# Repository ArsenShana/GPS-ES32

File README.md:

# AlanaTech GPS — трекер на ESP32 + LoRa E32

```
 [NEO-6M] ──UART──> [ESP32 трекер] ──[E32 433 МГц]))) ~~~ (((  [E32]──> [ESP32 приёмник] ──Wi-Fi──> браузер
```

| Папка | Что это |
|---|---|
| [gps_tracker/](gps_tracker/) | ESP32 + NEO-6M + E32: раз в 5 с отправляет координаты по радио |
| [gps_receiver/](gps_receiver/) | ESP32 + E32: принимает пакеты, подключается к Wi-Fi `New BilimLand Wi-Fi`, показывает карту |

Оба проекта — PlatformIO (VS Code → расширение PlatformIO IDE).

## Плата без проводов и 3D-модель

В `tracker-lab/` добавлены локальный сайт с интерактивной 3D-моделью, симуляция
радиообмена, программно разведённая плата-носитель KiCad и корпус STL/STEP.
Запуск сайта: `cd tracker-lab` → `npm ci` → `npm start`, затем открыть
`http://localhost:4173`. Инструкция по сборке и прошивке: `tracker-lab/README.html`.

Носитель R0 рассчитан на **ESP32-DevKitC V4 WROOM с 38 контактами**, NEO-6M
breakout и E32-433T30D. Это прототип: разъёмы нужно сверить с вашими модулями,
KiCad DRC/ERC и физические испытания ещё не выполнены. Герберы пока не выпущены.
Для носителя добавлены среды `carrier` и `carrier_fake` с AUX на GPIO19;
передача пропускается при ошибке конфигурации E32 или таймауте AUX.

Вторая версия **AT-02 V2** находится в `tracker-lab/v2/` и открывается по
`http://localhost:4173/v2/`. Это собственная SMD-архитектура на STM32L072CBT6
с MAX-M10S, E32-433T20S, USB-C, LiPo/PowerPath, buck-boost 3.3 В и датчиком
движения. Arduino/ESP32-DevKit не используются. Подготовлены нумерованная
KiCad-схема, netlist, компоновка PCB 68×44 мм, корпус и отдельная 3D-модель.
Статус V2 — инженерный проект A0: финальная трассировка, RF, уточнение некоторых
посадочных мест и DRC/ERC ещё нужны; Gerber не выпущены. Ядро логики написано
на C и проверено на компьютере, но полный STM32-порт и физические испытания
пока не выполнены. ESP32-прошивку R0 нельзя загружать в V2.

## Подключение

E32 — одинаково на обеих платах:

| E32-433T30D | ESP32 трекер | ESP32 приёмник |
|---|---|---|
| VCC | **5V (VIN)** — не 3.3V! | **5V (VIN)** |
| GND | GND | GND |
| TXD | GPIO16 | GPIO16 |
| RXD | GPIO17 | GPIO17 |
| M0 | GPIO25 | GPIO25 |
| M1 | GPIO26 | GPIO26 |
| AUX | GPIO27 (можно не подключать) | GPIO27 (можно не подключать) |

Только на трекере — NEO-6M (без GPS прошивайте `tracker_fake`):

| NEO-6M | ESP32 |
|---|---|
| VCC | 3.3V (или 5V, если на модуле есть стабилизатор) |
| GND | GND |
| TX | GPIO32 |
| RX | GPIO33 |

> ⚠️ **Никогда не включайте E32 без антенны** — на мощности 1 Вт выходной каскад сгорит.
> ⚠️ E32-433T30D при передаче берёт до ~700 мА. Питание от USB ноутбука может «проседать» —
> тогда ESP32 перезагружается (brownout). Поставьте конденсатор 470–1000 мкФ между VCC и GND модуля.
> При тесте на столе антенны должны быть на расстоянии хотя бы 1–2 м (1 Вт вплотную перегружает приёмник).

Пины меняются в `include/config.h` каждого проекта.

## Параметры радио

Обе прошивки при старте сами проверяют и при необходимости записывают одинаковую конфигурацию E32:
433 МГц (канал 0x17), адрес 0x0000, UART 9600, скорость в эфире 2.4 кбит/с, FEC, 30 дБм, прозрачный режим.

Формат пакета (≤ 58 байт, один радиопакет E32) описан в `lib/GpsProtocol/GpsProtocol.h`:
```
G,1,1234,1,51.128207,71.430411,347,12.3,9,0.9*50
```

## Прошивка

Плата подключается по Type-C и видна как `USB-SERIAL CH340 (COMx)`. Если порт не появился —
кабель только для зарядки, нужен кабель с передачей данных.

**Режим прошивки.** На этих платах автоматический вход в загрузчик не срабатывает
(ошибка `Wrong boot mode detected (0x13)`), поэтому перед каждой прошивкой:
1. зажать **BOOT**;
2. нажать и отпустить **EN** (RST);
3. отпустить **BOOT** — плата ждёт прошивку, пока её не перезагрузят.

```bash
# трекер
cd gps_tracker
pio run -e tracker -t upload && pio device monitor

# приёмник
cd gps_receiver
pio run -e receiver -t upload && pio device monitor
```

Если PlatformIO не установлен в VS Code, вместо `pio` используйте `py -3.11 -m platformio`.

`lib/GpsProtocol` и `lib/E32` одинаковые в обеих папках — при изменении правьте обе копии.

Ход тестирования и найденные ошибки — в [TESTING.md](TESTING.md).

## Тестирование

### 1. Юнит-тесты протокола (без железа, на ПК)
```bash
cd gps_tracker  && pio test -e native
cd gps_receiver && pio test -e native
```
Проверяют кодирование/декодирование, отбрасывание битых и обрезанных пакетов, помещение в 58 байт, подсчёт потерь.
Нужен gcc в PATH (например, MSYS2 `C:\msys64\mingw64\bin`).

### 2. Проверка каждого модуля (Serial-монитор, 115200)
- Трекер: должно быть `[E32] конфигурация ОК` и строки `[GPS] символов=...` с растущим числом.
  Если `символов=0` — неправильно подключён TX NEO-6M.
- Приёмник: `[E32] конфигурация ОК`, `[WiFi] подключено, IP: ...`.
  Если Wi-Fi не подключился, прошивка печатает код причины и список видимых сетей
  (201 — сеть не найдена: проверьте имя с учётом регистра и что сеть на 2.4 ГГц).

### 3. Радиоканал без GPS (в помещении)
Прошейте трекер тестовой прошивкой — она шлёт координаты по кругу вокруг центра Астаны:
```bash
cd gps_tracker && pio run -e tracker_fake -t upload
```
В логе приёмника появятся строки `[RX] id=1 seq=... fix=1 ...`, на странице `http://<IP приёмника>/` — движущаяся точка.

### 4. Автоматическая проверка связи с ПК
ПК должен быть в той же Wi-Fi сети:
```bash
python gps_receiver/tools/link_test.py <IP приёмника> -t 120
```
В конце — итог: принято / потеряно / % потерь и вердикт.

### 5. Настоящий GPS
Прошейте `-e tracker`, вынесите трекер на улицу или к окну. Холодный старт NEO-6M — до 5 минут
(на модуле замигает светодиод, когда есть фикс). На странице бейдж станет «GPS фикс», на карте появится трек.

## Веб-интерфейс приёмника

| Адрес | Что |
|---|---|
| `/` | карта + данные |
| `/api/last` | последний пакет, JSON |
| `/api/history` | трек (до 200 точек), JSON |
| `/api/status` | статистика приёма, Wi-Fi |
| `POST /api/reset` | сброс статистики |

Также доступно по `http://alanatech-gps.local/` (если сеть/ОС поддерживает mDNS).
Карта грузится из интернета (OpenStreetMap), таблица работает и без него.

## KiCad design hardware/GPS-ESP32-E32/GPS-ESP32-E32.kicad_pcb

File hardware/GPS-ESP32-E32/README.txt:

GPS-ESP32-E32 — плата-носитель R0, 100 × 78 мм, 2 слоя, FR4 1.6 мм.

Открыть GPS-ESP32-E32.kicad_pro в KiCad. Рядом находятся редактируемая
схема .kicad_sch, разведённая плата .kicad_pcb, локальные библиотеки,
PDF схемы и платы, BOM.csv и отчёты DRC/ERC.

Модули: ESP32-DevKitC V4 WROOM, 38 контактов (19 на сторону,
25.4 мм между рядами); NEO-6M breakout; E32-433T30D.
J2/J3 — гнёзда ESP32, J4 — GPS, J5 — E32, J1 — вход 5 В.
GPS J4: 1=3V3, 2=RX, 3=TX, 4=GND.
E32 J5: 1=M0, 2=M1, 3=RXD, 4=TXD, 5=AUX, 6=5V, 7=GND.

Точная разводка GPIO:
GPS TX -> GPIO16, GPS RX <- GPIO17.
E32 TXD -> GPIO26, E32 RXD <- GPIO27.
E32 M0 <- GPIO25, E32 M1 <- GPIO18, E32 AUX -> GPIO19.
Индикатор: GPIO2 -> R1 330 Ом -> анод D1; катод D1 -> GND.

Прошивка из gps_tracker:
  pio run -e kicad_r0 -t upload
Для демонстрационных координат:
  pio run -e kicad_r0_fake -t upload
Обычные tracker/carrier имеют другую распиновку и не подходят этой разводке.

Питание: внешний стабилизированный источник 5 В / 2 А на J1.
E32 питается от 5 В, GPS — от 3.3 В ESP32. C1 1000 мкФ / 10 В
и C2 100 нФ установлены на шине 5 В возле радио.
JP1 соединяет внешний источник с 5V ESP32: снять перемычку до
подключения USB ESP32. Не подавать автомобильные 12/24 В напрямую.
Перед включением радио подключить подходящую антенну 433 МГц.

Проверено KiCad 10.0.6: DRC — 0 нарушений, 0 неподключённых;
ERC — 0 нарушений. Символы описывают пассивные контакты разъёмов:
ERC не проверяет внутренние цепи модулей и совместимость уровней.
Статус: прототип. До изготовления сверить габариты и порядок контактов
реальных модулей, гнёзда E32, полярность LED и конденсатора, проверить
питание и работу на стенде. Геометрия SMD-площадок упрощена.
Герберы для производства не выпускались.

Повторный экспорт проекта:
  python3 tracker-lab/tools/export_kicad_project.py
PDF и DRC/ERC обновляются отдельно через kicad-cli.

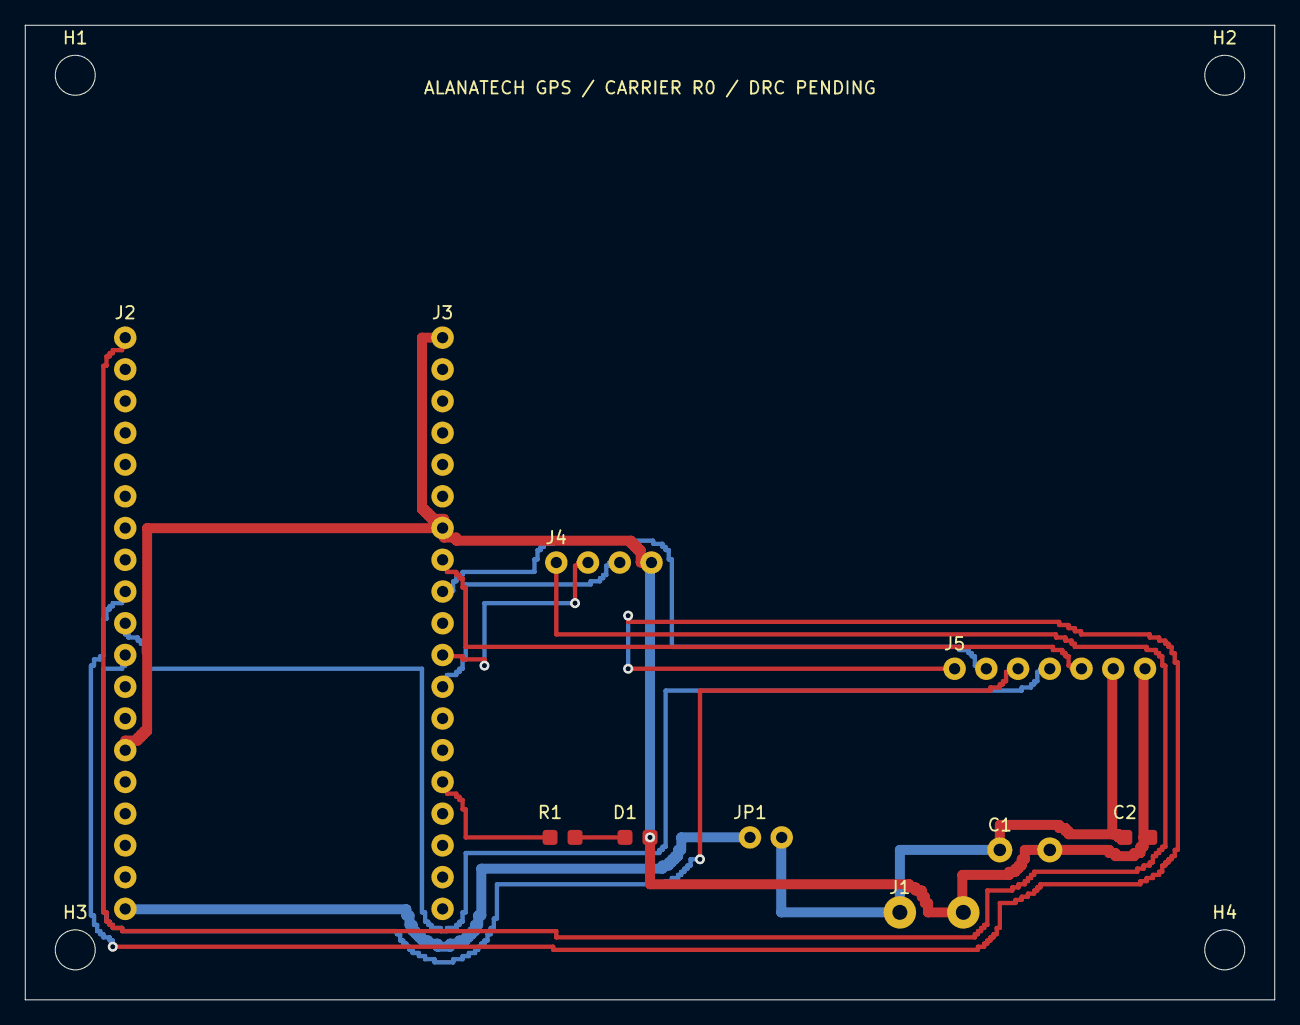
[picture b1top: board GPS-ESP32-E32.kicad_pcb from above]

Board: 2 copper layers, 100.0 x 78.0 mm, 14 parts (0 on the bottom side), 13 nets.

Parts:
C1: 1000uF_10V
C2: 100nF_0805
D1: LED_0805
H1, H2, H3, H4: M3
J1: 5V_INPUT_2A
J2: ESP32_J2_1x19
J3: ESP32_J3_1x19
J4: NEO6M_SOCKET_1x04
J5: E32_SOCKET_1x07_RIGHT_ANGLE
JP1: REMOVE_FOR_USB
R1: 330R_0805

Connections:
+3V3: J2.1, J4.1
+5V_ESP: J2.19, JP1.1
+5V_MAIN: C1.1, C2.1, J1.1, J5.6, JP1.2
E32_AUX: J3.8, J5.5
E32_M0: J2.9, J5.1
E32_M1: J3.9, J5.2
E32_RXD: J2.11, J5.3
E32_TXD: J2.10, J5.4
GND: C1.2, C2.2, D1.2, J1.2, J2.14, J3.1, J3.7, J4.4, J5.7
GPS_RX: J3.11, J4.2
GPS_TX: J3.12, J4.3
LED_A: D1.1, R1.2
LED_GPIO: J3.15, R1.1

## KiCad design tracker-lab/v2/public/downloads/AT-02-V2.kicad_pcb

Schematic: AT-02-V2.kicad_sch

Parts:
C1: 100nF / VDD1
C2: 100nF / VDD24
C3: 100nF / VDD48
C4: 100nF / USB VDD
C5: 100nF / VDDA
C6: 4.7uF / MCU
C7: 100nF / reset
C8: 100nF / ADC
C9: 1uF / GNSS VIO
C10: 10uF / GNSS VCC
C11: 1uF / GNSS backup
C12: 100nF / motion
C13: 10uF / motion
C14: 10uF / USB IN
C15: 10uF / battery
C16: 22uF / VSYS
C17: 10uF / buck-boost IN
C18, C19: 22uF / buck-boost OUT
C20: 100uF / radio buffer
C21: 100nF / radio
D1: Green LED / status
FB1: Ferrite / analog supply
J1: USB-C / USB 2.0
J2: LiPo / NTC · 3 контакта
J3: GNSS RF / u.FL
J4: SWD / pogo
L1: Дроссель 2.2 µH
R1: 5.1k / CC1
R2: 5.1k / CC2
R3: 22R / USB D+
R4: 22R / USB D-
R5: 10k / BOOT0
R6: 10k / NRST
R7: 1M / battery divider
R8: 330k / battery divider
R9: 10k / I2C SCL
R10: 10k / I2C SDA
R11: 330R / LED
R12: 100k / EN1 default
R13: 2.94k / ISET 300mA target
R14: 3.24k / ILIM
R15: 46.4k / safety timer
R16: 1k / ITERM
R17: 10k / CHG pullup
R18: 100R / GNSS QOD
R19: 10k / radio reset pullup
R20: 100k / M0 pulldown
R21: 100k / M1 pulldown
SW1: BOOT / DFU
SW2: RESET
U1: STM32L072CBT6
U2: u-blox MAX-M10S
U3: EBYTE E32-433T20S
U4: TI BQ24074
U5: TI TPS63031
U6: ST LIS2DW12
U7: TI TPS22919
U8: USBLC6-2SC6 / ESD

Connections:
+3V3: C1.1, C2.1, C3.1, C4.1, C6.1, C11.1, C12.1, C13.1, C18.1, C19.1, C20.1, C21.1, FB1.1, J4.1 (+3V3), R6.2, R9.2, R10.2, R17.2, R19.2, SW1.2 (3V3), U1.1 (VDD), U1.24 (VDD), U1.36 (VDD_USB), U1.48 (VDD), U2.6 (V_BCKP), U3.25 (VCC), U5.1 (VOUT), U5.10 (FB), U6.2 (CS), U6.9 (VDD), U6.10 (VDD_IO), U7.1 (VIN)
+3V3_A: C5.1, FB1.2, U1.9 (VDDA)
+3V3_GNSS: C9.1, C10.1, R18.2, U2.7 (V_IO), U2.8 (VCC), U7.6 (VOUT)
BAT_NTC: J2.3 (BAT_NTC), U4.1 (TS)
BOOT0: R5.1, SW1.1 (BOOT0), U1.44 (BOOT0)
CHARGE_EN1: R12.1, U1.45 (PB8), U4.6 (EN1)
CHG_ILIM: R14.1, U4.12 (ILIM)
CHG_ISET: R13.1, U4.16 (ISET)
CHG_ITERM: R16.1, U4.15 (ITERM)
CHG_STATUS: R17.1, U1.46 (PB9), U4.9 (CHG)
CHG_TMR: R15.1, U4.14 (TMR)
GND: C1.2, C2.2, C3.2, C4.2, C5.2, C6.2, C7.2, C8.2, C9.2, C10.2, C11.2, C12.2, C13.2, C14.2, C15.2, C16.2, C17.2, C18.2, C19.2, C20.2, C21.2, D1.2, J1.A1, J1.A12, J1.B1, J1.B12, J1.S1 (SHIELD), J1.S2 (SHIELD), J1.S3 (SHIELD), J1.S4 (SHIELD), J2.2 (GND), J3.2 (GND), J3.3 (GND), J4.5 (GND), R1.2, R2.2, R5.2, R8.2, R12.2, R13.2, R14.2, R15.2, R16.2, R20.2, R21.2, SW2.2 (GND), U1.8 (VSSA), U1.23 (VSS), U1.35 (VSS), U1.47 (VSS), U2.1 (GND), U2.10 (GND), U2.12 (GND), U3.2 (GND), U3.8 (GND), U3.11 (GND), U3.13 (GND), U3.14 (GND), U3.15 (GND), U3.16 (GND), U3.19 (GND), U3.26 (GND), U4.4 (CE), U4.5 (EN2), U4.8 (VSS), U4.17 (EP), U5.3 (PGND), U5.7 (PS_SYNC), U5.9 (GND), U5.11 (EP), U6.3 (SDO_SA0), U6.6 (GND), U6.7 (RES), U6.8 (GND), U7.2 (GND), U8.2
GNSS_EN: U1.16 (PA6), U7.3 (ON)
GNSS_PPS: U1.17 (PA7), U2.4 (TIMEPULSE)
GNSS_QOD: R18.1, U7.4 (QOD)
GNSS_RF: J3.1 (RF), U2.11 (RF_IN)
GNSS_RX: U1.30 (PA9), U2.3 (RXD)
GNSS_TX: U1.31 (PA10), U2.2 (TXD)
I2C_SCL: R9.1, U1.42 (PB6), U6.1 (SCL)
I2C_SDA: R10.1, U1.43 (PB7), U6.4 (SDA)
LED_A: D1.1, R11.2
LED_DRIVE: R11.1, U1.41 (PB5)
MOTION_INT: U1.19 (PB1), U6.12 (INT1)
NRST: C7.1, J4.4 (NRST), R6.1, SW2.1 (NRST), U1.7 (NRST)
RADIO_AUX: U1.11 (PA1), U3.24 (AUX)
RADIO_M0: R20.1, U1.14 (PA4), U3.20 (M0)
RADIO_M1: R21.1, U1.15 (PA5), U3.21 (M1)
RADIO_RESET: R19.1, U1.18 (PB0), U3.1 (RESET)
RADIO_RX: U1.12 (PA2), U3.22 (RXD)
RADIO_TX: U1.13 (PA3), U3.23 (TXD)
SWCLK: J4.3 (SWCLK), U1.37 (PA14)
SWDIO: J4.2 (SWDIO), U1.34 (PA13)
SW_L1: L1.1 (L1), U5.4 (L1)
SW_L2: L1.2 (L2), U5.2 (L2)
USB_CC1: J1.A5, R1.1
USB_CC2: J1.B5, R2.1
USB_DM: R4.2, U1.32 (PA11)
USB_DM_CONN: J1.A7, J1.B7, R4.1, U8.3, U8.4
USB_DP: R3.2, U1.33 (PA12)
USB_DP_CONN: J1.A6, J1.B6, R3.1, U8.1, U8.6
VBAT: C15.1, J2.1 (VBAT), R7.1, U4.2 (BAT), U4.3 (BAT)
VBAT_ADC: C8.1, R7.2, R8.1, U1.10 (PA0)
VBUS: C14.1, J1.A4, J1.A9, J1.B4, J1.B9, U4.13 (IN), U8.5
VSYS: C16.1, C17.1, U4.10 (OUT), U4.11 (OUT), U5.5 (VIN), U5.6 (EN), U5.8 (VINA)

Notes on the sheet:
AT-02 V2 A0 - CONNECTIVITY DRAFT / Verify package lands, RF, ERC pin types and complete routing before release

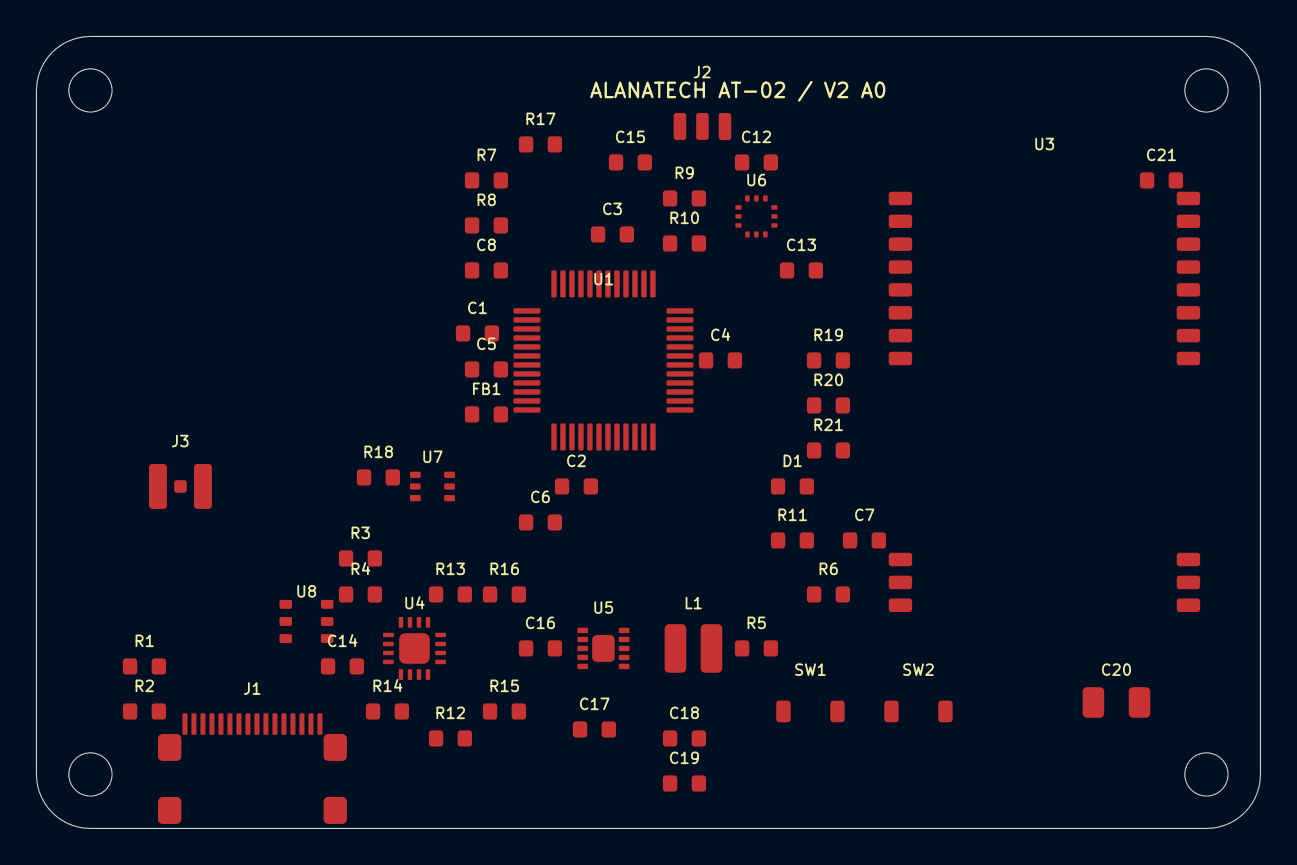
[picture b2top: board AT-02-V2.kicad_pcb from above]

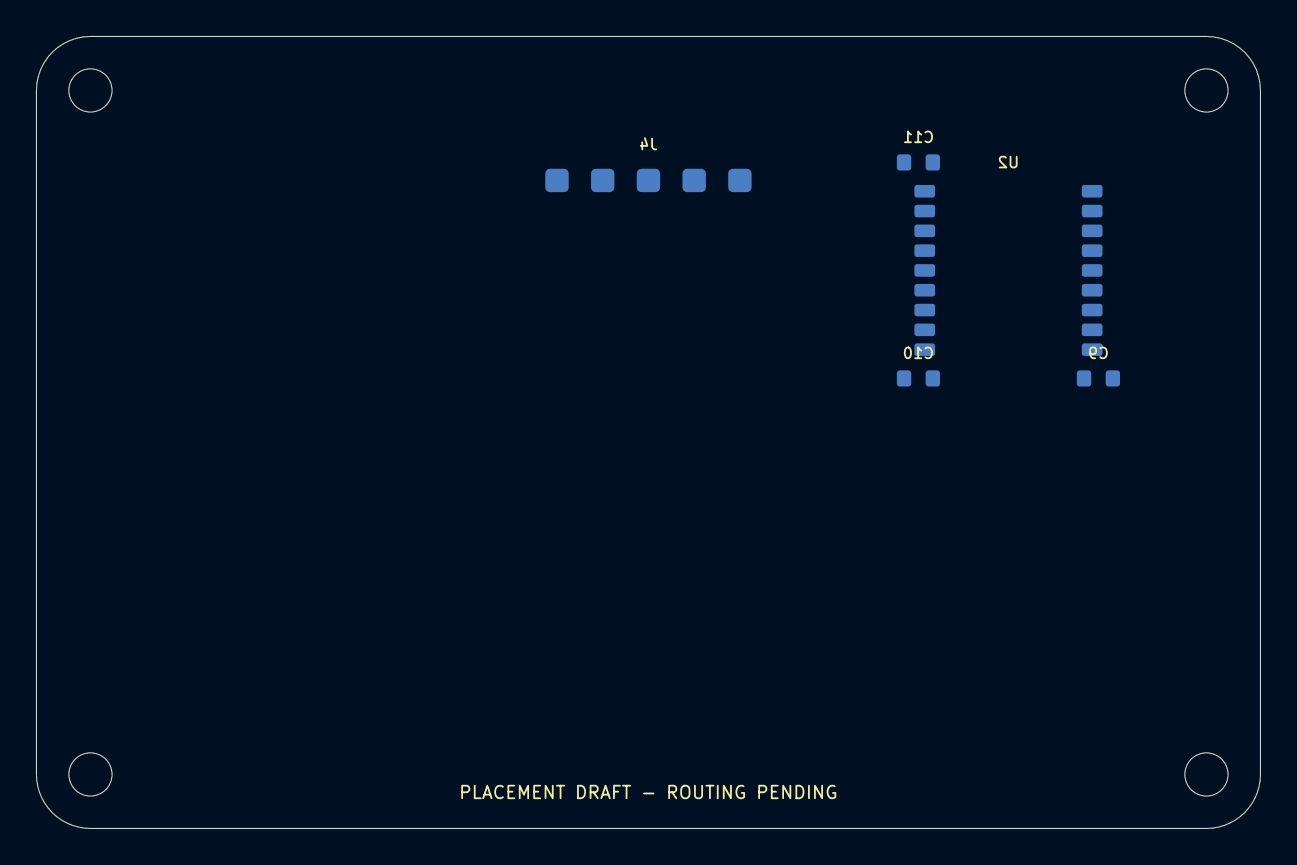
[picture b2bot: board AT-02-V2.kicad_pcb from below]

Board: 4 copper layers, 68.0 x 44.0 mm, 59 parts (5 on the bottom side), 44 nets, no tracks yet.

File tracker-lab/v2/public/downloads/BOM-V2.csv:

Ref,Value,Layer,X mm,Y mm,Status
U1,STM32L072CBT6,F.Cu,31.5,18,Selection/land pattern verification required
U2,u-blox MAX-M10S,B.Cu,14,13,Selection/land pattern verification required
U3,EBYTE E32-433T20S,F.Cu,56,20,Selection/land pattern verification required
U4,TI BQ24074,F.Cu,21,34,Selection/land pattern verification required
U5,TI TPS63031,F.Cu,31.5,34,Selection/land pattern verification required
U6,ST LIS2DW12,F.Cu,40,10,Selection/land pattern verification required
U7,TI TPS22919,F.Cu,22,25,Selection/land pattern verification required
J1,USB-C / USB 2.0,F.Cu,12,41,Selection/land pattern verification required
J2,LiPo / NTC · 3 контакта,F.Cu,37,5,Selection/land pattern verification required
L1,Дроссель 2.2 µH,F.Cu,36.5,34,Selection/land pattern verification required
J3,GNSS RF / u.FL,F.Cu,8,25,Selection/land pattern verification required
SW1,BOOT / DFU,F.Cu,43,37.5,Selection/land pattern verification required
SW2,RESET,F.Cu,49,37.5,Selection/land pattern verification required
R1,5.1k / CC1,F.Cu,6,35,Selection/land pattern verification required
R2,5.1k / CC2,F.Cu,6,37.5,Selection/land pattern verification required
R3,22R / USB D+,F.Cu,18,29,Selection/land pattern verification required
R4,22R / USB D-,F.Cu,18,31,Selection/land pattern verification required
R5,10k / BOOT0,F.Cu,40,34,Selection/land pattern verification required
R6,10k / NRST,F.Cu,44,31,Selection/land pattern verification required
R7,1M / battery divider,F.Cu,25,8,Selection/land pattern verification required
R8,330k / battery divider,F.Cu,25,10.5,Selection/land pattern verification required
R9,10k / I2C SCL,F.Cu,36,9,Selection/land pattern verification required
R10,10k / I2C SDA,F.Cu,36,11.5,Selection/land pattern verification required
R11,330R / LED,F.Cu,42,28,Selection/land pattern verification required
R12,100k / EN1 default,F.Cu,23,39,Selection/land pattern verification required
R13,2.94k / ISET 300mA target,F.Cu,23,31,Selection/land pattern verification required
R14,3.24k / ILIM,F.Cu,19.5,37.5,Selection/land pattern verification required
R15,46.4k / safety timer,F.Cu,26,37.5,Selection/land pattern verification required
R16,1k / ITERM,F.Cu,26,31,Selection/land pattern verification required
R17,10k / CHG pullup,F.Cu,28,6,Selection/land pattern verification required
R18,100R / GNSS QOD,F.Cu,19,24.5,Selection/land pattern verification required
R19,10k / radio reset pullup,F.Cu,44,18,Selection/land pattern verification required
R20,100k / M0 pulldown,F.Cu,44,20.5,Selection/land pattern verification required
R21,100k / M1 pulldown,F.Cu,44,23,Selection/land pattern verification required
C1,100nF / VDD1,F.Cu,24.5,16.5,Selection/land pattern verification required
C2,100nF / VDD24,F.Cu,30,25,Selection/land pattern verification required
C3,100nF / VDD48,F.Cu,32,11,Selection/land pattern verification required
C4,100nF / USB VDD,F.Cu,38,18,Selection/land pattern verification required
C5,100nF / VDDA,F.Cu,25,18.5,Selection/land pattern verification required
C6,4.7uF / MCU,F.Cu,28,27,Selection/land pattern verification required
C7,100nF / reset,F.Cu,46,28,Selection/land pattern verification required
C8,100nF / ADC,F.Cu,25,13,Selection/land pattern verification required
C9,1uF / GNSS VIO,B.Cu,9,19,Selection/land pattern verification required
C10,10uF / GNSS VCC,B.Cu,19,19,Selection/land pattern verification required
C11,1uF / GNSS backup,B.Cu,19,7,Selection/land pattern verification required
C12,100nF / motion,F.Cu,40,7,Selection/land pattern verification required
C13,10uF / motion,F.Cu,42.5,13,Selection/land pattern verification required
C14,10uF / USB IN,F.Cu,17,35,Selection/land pattern verification required
C15,10uF / battery,F.Cu,33,7,Selection/land pattern verification required
C16,22uF / VSYS,F.Cu,28,34,Selection/land pattern verification required
C17,10uF / buck-boost IN,F.Cu,31,38.5,Selection/land pattern verification required
C18,22uF / buck-boost OUT,F.Cu,36,39,Selection/land pattern verification required
C19,22uF / buck-boost OUT,F.Cu,36,41.5,Selection/land pattern verification required
C20,100uF / radio buffer,F.Cu,60,37,Selection/land pattern verification required
C21,100nF / radio,F.Cu,62.5,8,Selection/land pattern verification required
FB1,Ferrite / analog supply,F.Cu,25,21,Selection/land pattern verification required
D1,Green LED / status,F.Cu,42,25,Selection/land pattern verification required
U8,USBLC6-2SC6 / ESD,F.Cu,15,32.5,Selection/land pattern verification required
J4,SWD / pogo,B.Cu,34,8,Selection/land pattern verification required
ANT1,GNSS patch 18x18 - MPN and matching pending,F.Cu,14,13,RF validation required
BAT1,Protected LiPo 1S + NTC / 50x30x6 max,Off-board,9,7,Capacity chosen after current measurement

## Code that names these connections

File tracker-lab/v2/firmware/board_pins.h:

#ifndef AT02_BOARD_PINS_H
#define AT02_BOARD_PINS_H
/* STM32L072CBT6 / LQFP48; alternate functions verified in STM32 DS10689.
 * Port driver must configure these with CMSIS/LL and high-impedance GNSS UART
 * when +3V3_GNSS is off. This file does not initialize peripherals. */
#define AT_GNSS_UART "USART1: PA9 TX(AF4), PA10 RX(AF4), 9600 8N1"
#define AT_RADIO_UART "USART2: PA2 TX(AF4), PA3 RX(AF4), 9600 8N1"
#define AT_I2C "I2C1: PB6 SCL(AF1), PB7 SDA(AF1)"
#define AT_RADIO_AUX "PA1"
#define AT_RADIO_M0 "PA4"
#define AT_RADIO_M1 "PA5"
#define AT_RADIO_RESET "PB0"
#define AT_GNSS_ENABLE "PA6"
#define AT_GNSS_PPS "PA7"
#define AT_MOTION_INTERRUPT "PB1 / EXTI1"
#define AT_BATTERY_ADC "PA0 / ADC_IN0 / divider 1M:330k"
#define AT_LED "PB5"
#define AT_CHARGE_EN1 "PB8 / default LOW USB100; HIGH only after permitted USB budget"
#define AT_CHARGE_STATUS "PB9 / active LOW open-drain"
#define AT_USB "PA11 DM, PA12 DP / HSI48 + CRS"
#define AT_SWD "PA13 SWDIO, PA14 SWCLK, NRST"
#endif

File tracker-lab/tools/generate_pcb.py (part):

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
left = ["3V3","EN","VP","VN","IO34","IO35","IO32","IO33","IO25","IO26","IO27","IO14","IO12","GND","IO13","D2","D3","CMD","5V"]
right = ["GND","IO23","IO22","TX","RX","IO21","GND","IO19","IO18","IO5","IO17","IO16","IO4","IO0","IO2","IO15","D1","D0","CLK"]
net_by_name = {"3V3":"+3V3", "GND":"GND", "5V":"+5V_ESP", "IO25":"E32_M0", "IO26":"E32_TXD", "IO27":"E32_RXD", "IO19":"E32_AUX", "IO18":"E32_M1", "IO17":"GPS_RX", "IO16":"GPS_TX", "IO2":"LED_GPIO"}
for ref, x, names in [("J2",8,left),("J3",33.4,right)]:
    for i,name in enumerate(names):
        pad(ref,i+1,name,net_by_name.get(name,""),x,25+i*2.54)
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pad("C1",2,"-","GND",82,66,2,1)
pad("C2",1,"1","+5V_MAIN",88,65,1.2,0)
pad("C2",2,"2","GND",90,65,1.2,0)
pad("R1",1,"1","LED_GPIO",42,65,1.2,0)
pad("R1",2,"2","LED_A",44,65,1.2,0)
pad("D1",1,"A","LED_A",48,65,1.2,0)
pad("D1",2,"K","GND",50,65,1.2,0)
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def generate():
    OUT.mkdir(parents=True,exist_ok=True)
    import random
    presets=[['LED_GPIO','LED_A','+5V_ESP','+5V_MAIN','GND','+3V3'],
             ['+5V_ESP','+5V_MAIN','GND','+3V3','LED_GPIO','LED_A'],
             ['GND','+5V_MAIN','+5V_ESP','+3V3','LED_GPIO','LED_A']]
    rng=random.Random(42)
    for attempt in range(20):
        TRACES.clear();VIAS.clear()
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    netlist.append('))');(OUT/"carrier.net").write_text("\n".join(netlist)+"\n")

def write_schematic():
    rows=[("GPS TX → ESP RX","JGPS.3","GPIO16 / J3.12","GPS_TX"),
          ("ESP TX → GPS RX","GPIO17 / J3.11","JGPS.2","GPS_RX"),
          ("E32 TXD → ESP RX","JE32.4","GPIO26 / J2.10","E32_TXD"),
          ("ESP TX → E32 RXD","GPIO27 / J2.11","JE32.3","E32_RXD"),
          ("Режим радио M0","GPIO25 / J2.9","JE32.1","E32_M0"),
          ("Режим радио M1","GPIO18 / J3.9","JE32.2","E32_M1"),
          ("Готовность AUX","JE32.5","GPIO19 / J3.8","E32_AUX"),
          ("Питание GPS","3V3 / J2.1","JGPS.1","+3V3"),
          ("Питание E32","JPOWER.1 / 5V","JE32.6, C1+, C2.1","+5V_MAIN"),
          ("Питание ESP32","5V → JP1 → J2.19","Снять JP1 при USB","+5V_ESP"),
          ("Общая земля","JPOWER.2","J2.14 / J3.1,7 / GPS.4 / E32.7","GND"),
          ("Индикатор TX","GPIO2 / J3.15","R1 330Ω → D1 → GND","LED_GPIO")]
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    for i,(title,a,b,net) in enumerate(rows):
        y=108+i*40
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
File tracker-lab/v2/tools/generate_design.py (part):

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
# USB footprint represents a 16-contact USB2 receptacle; selection and shell
# locating pegs need to be locked to a particular MPN in the release BOM.
usb_pins=[("A1","GND"),("A4","VBUS"),("A5","USB_CC1"),("A6","USB_DP_CONN"),("A7","USB_DM_CONN"),("A8",""),("A9","VBUS"),("A12","GND"),("B1","GND"),("B4","VBUS"),("B5","USB_CC2"),("B6","USB_DP_CONN"),("B7","USB_DM_CONN"),("B8",""),("B9","VBUS"),("B12","GND")]
for i,(num,net) in enumerate(usb_pins):pin("J1",num,num,net,(i-7.5)*.5,-2.8,.28,1.2)
for i,(dx,dy) in enumerate([(-4.6,-1.5),(4.6,-1.5),(-4.6,2),(4.6,2)]):pin("J1","S"+str(i+1),"SHIELD","GND",dx,dy,1.3,1.5)
for i,net in enumerate(["VBAT","GND","BAT_NTC"]):pin("J2",i+1,net,net,(i-1)*1.25,0,.7,1.5)
pin("J3",1,"RF","GNSS_RF",0,0,.7,.7)
pin("J3",2,"GND","GND",-1.25,0,1,2.5);pin("J3",3,"GND","GND",1.25,0,1,2.5)
pin("L1",1,"L1","SW_L1",-1,0,1.2,2.7);pin("L1",2,"L2","SW_L2",1,0,1.2,2.7)
for ref,net in [("SW1","BOOT0"),("SW2","NRST")]:
    pin(ref,1,net,net,-1.5,0,.8,1.2);pin(ref,2,"3V3" if ref=="SW1" else "GND","+3V3" if ref=="SW1" else "GND",1.5,0,.8,1.2)

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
